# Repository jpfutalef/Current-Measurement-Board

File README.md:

# Power-Monitoring-Board
This repo contains scripts, details and specifications for a board designed to measure very low power consumption in MCU's with high accuracy.

## Goals

The goal here is to develop a simple current measuring board that can measure from 1uA - 50mA at high frequencies (>10kHz).

This board has to be easy to connect to a computer or a raspberry, minimizing cable connections. The idea is to have a single board with two usb ports, one to connect to the PC and the other to an IoT node with any usb connection (micro, mini, etc.).

## Organization

The repo is organized as follows,

* **ltspice**: in this folder can be found the different spice schematics to simulate the different current measurement boards.
* **scripts**: in this folder can be found different c, python, etc. scripts used to read data from the current measurement circuit or calibrate the respective board.
* **boards**: the actual eagle schematics can be found in this folder, either for the circuits or breakout's for small smd-components.

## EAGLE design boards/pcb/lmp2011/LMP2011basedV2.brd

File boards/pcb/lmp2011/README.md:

# PCB eagle schematics and boards for LMP2011

LMP2011 is a precision OPAMP. This device uses auto-zero techniques to continually correct the input offset error voltage. The input offset is 60uV in the worst case scenario,  0.8uV typically. Furthermore has a typical CMRR of 130dB, its minimum is 95dB.

## Notations
* Current Measuring Board (CMB): PCB with the designed circuit that can measure shunt voltage, and supply voltage.
* mcu: microcontroller connected to the CMB, its performs calibrations and translate the supply voltage and current measurements.
* Node: target mcu which power consumption the CMB is measuring.

## How to use

* Connect switch controllers (SWITCH_CTRL_1 to SWITCH_CTRL_5) to 5 different GPIO on any mcu.
* Connect low current, high current and supply voltage to 3 different ADC input in the mcu
* Power the CMB, either from the micro usb port or with 5V from an external power supply
* Bypass the targeted node power supply by either connecting it's power source to VBAT or the USB port on CMB.
* If the targeted node supply source is connected to VBAT then the node can be powered by connecting it's power input to VMCU, if it's USB powered a jumper must be connected between 5V and VBAT on CMB.

## Specifications:
- Power supply: 5V from USB port
- Current range: ~10uA - 50mA
- First stage gain: x100
- Second stage gain: x197 for low current, x1.51 for high current

## How version 2 works(detailed)

This board has a similar operation as the design using MAX4239, except that in this case the CMB does not include a DC booster (TODO: check if it is neccesary).

### Fist stage

The first stage amplifies the voltage difference in the shunt resistance through an OPAMP. R1, R2, R4 and R5 form a x100 gain between VBAT y VS-. R27 and C2 are added for stability purposes. 

### Second stage

The second stage has a LTC6241 high precision dual opamp. There are two current ranges with different gains:

- Low current range: 0uA-600uA, x197 gain
- High current tange: 600uA-50mA, x1.51 gain

These gains values adjust to the ADC input ranges. The 49.9 resistor are put in place to isolate the amplifier output and ADC input, thus preventing oscillation.

4 usually open analog switches are used for calibration in low current, this is done by measuring current flow threw resistors R9, R10, R13 and R14. TS5A23166DCUR switches where chosen for their high voltage input range, high max current and low Ron (0.8 ohms).

A normally closed switch is connected between the target node and it's supply source. The TS5A23167DCUR was chosen with similar characteristics as the TS5A23167DCUR.

C1 capacitor is connected between the supply source and ground to stabilize supply voltage from power source.

The buffer stage to measure the supply source uses a LTC6240 high precision amplifier with a x0.5 gain stage to allow supply voltage higher than the mcu supply (3.3V) to be converted with the ADC. This buffer stages also isolated the two.

As a supply source a microUSB type B female connector is used. This gives a 5V power supply. To reduce high frequency noise a high impedance, low frequency ferrite is used (1K@1Mhz).

A female type A USB connector can be used to power the targeted node. Analog and digital ground are separated by using two schottky diodes, CUS08F30 because of their high response and low activation voltage.

### Available connections

Multiple input/output pins are exposed to users: 

- SWITCH_CTRL_1: switch's on power supply for targeted node.
- SWITCH_CTRL_2 a 5: switches on or off calibration resistors.
- VMCU: output voltage that powers the targeted node it's short-circuited to the female type A USB.
- GND: ground
- OUT_STAGE1: first amplifying stage gain output, for debugging purposes.
- VS-: shunt resistor low voltage pin.
- VBAT: pin where targeted node supply voltage is connected to bypass it.
- +5V: 5V output, its separated from the USB by the ferrite. de 5V, separada de USB por la ferrita.

# Board versions

## LMP2011 V1 - Fabricated
This version of the board was manufactured with [OSHPARK](https://oshpark.com/). Soldering and testing was done at Inria Chile office.

### Overview

This board needs a 5V supply for most of the IC, LMP2011 get supply from a DC booster in the CMB.

The first stage is a differential amplifier with x10 gain, the second stage has a low current stage with x197 gain and a high current range with x1.51 gain.

To read supply voltage a x0.5 buffer stage is used.

Analog and digital ground are separate with schottky diodes.

5V supply source is filtered with a 1k@1MHz ferrite.

USB enclosure is connected to the digital ground.

### Testing conclusions

#### Remarks
- Manufactured board
- Soldered components
- All IC had correct supply and GND connections
- There is an error in power supply for the LMP2011 design: it can't be supply from 8v68. MIC2250 is not connected and bypass 5V to the supply pin of the IC.
- There aren't conclusive results from the circuit. The CMB with this IC does not work as it should, neither in a breadboard.

#### TODO
- Check connections in LMP2011
- Check real measurement range
- Make reading with a mcu. Calibrate and control of the switches

#### Issues
- LMP2011 not working correctly
- The gain in low current stage should be x197, not x19.7 10K resistance should be a 1K
- Control switch for node supply are not connected well. This was fixed soldering directly from the inputs of the switch
- Ad
- VBAT and VADC silkscreen names are misplaced, they are switched.
- There are no pull-down resistors in the control switch

#### To improve
- CMRR by using higher tolerance resistor values, at least 0.1%. This can also be done by incrementing the stages gain, but this affects the current ranges
- Change USB port from SMD to thru-hole to improve robustness in the pcb
- Different configurations for the first stage should be considered

## LMP2011 V2 - not manufactured

This version of the board should solve the issues from the last version manufactured.

* Remove DC booster (Check supply needed from the IC)
* Low current gain is addressed by changing 10K resistors to 1K
* Switch connection is fixed
* Pull down resistors are included for the switches

There is only the schematic for this board, not the board design yet

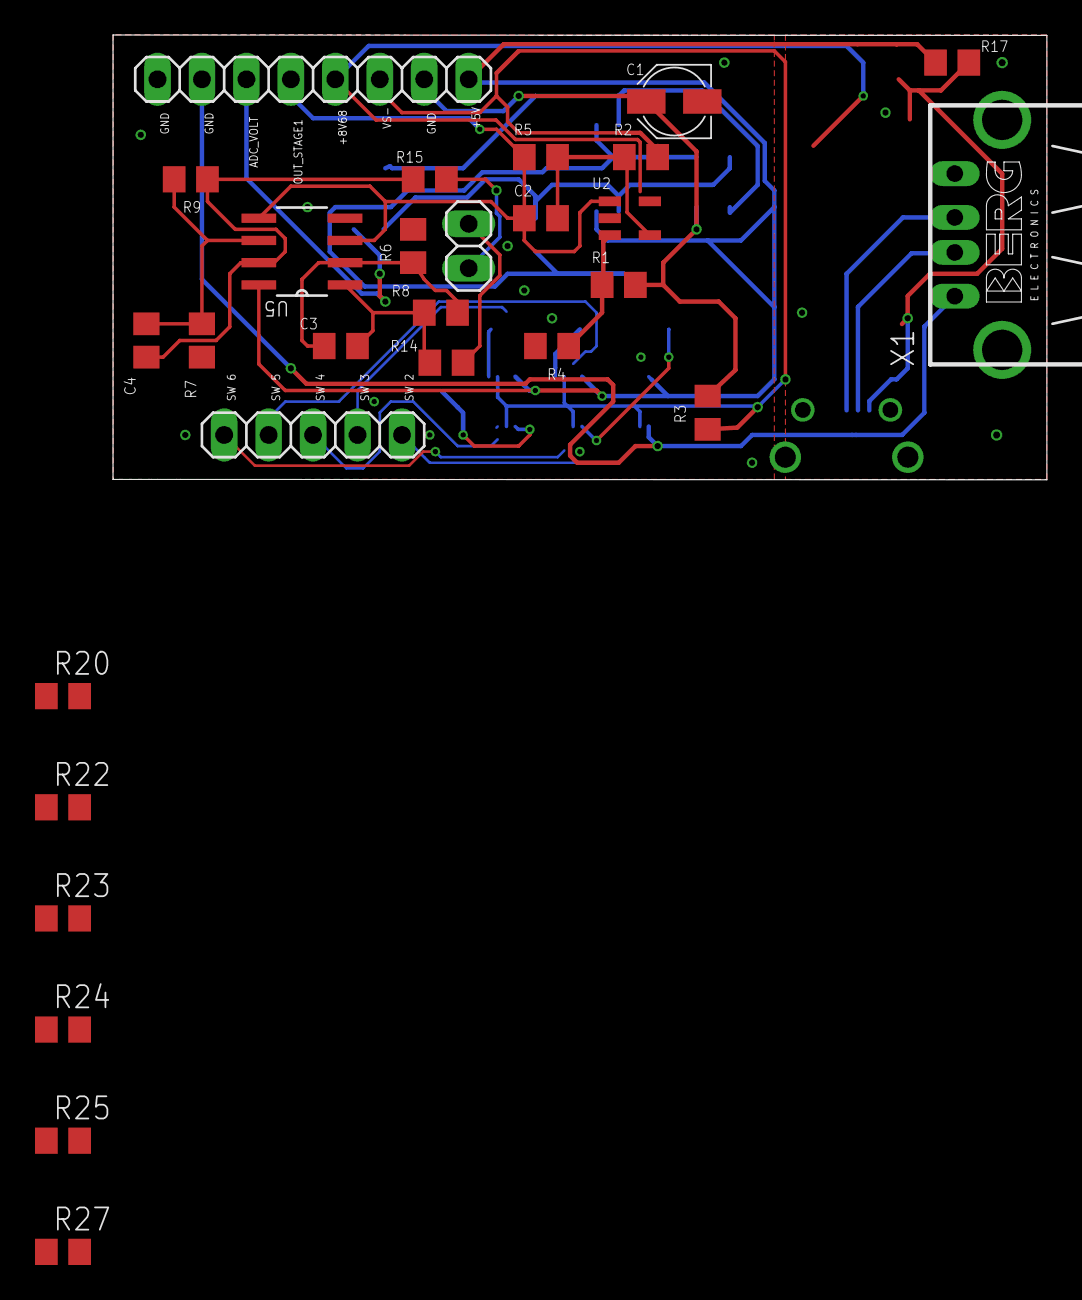
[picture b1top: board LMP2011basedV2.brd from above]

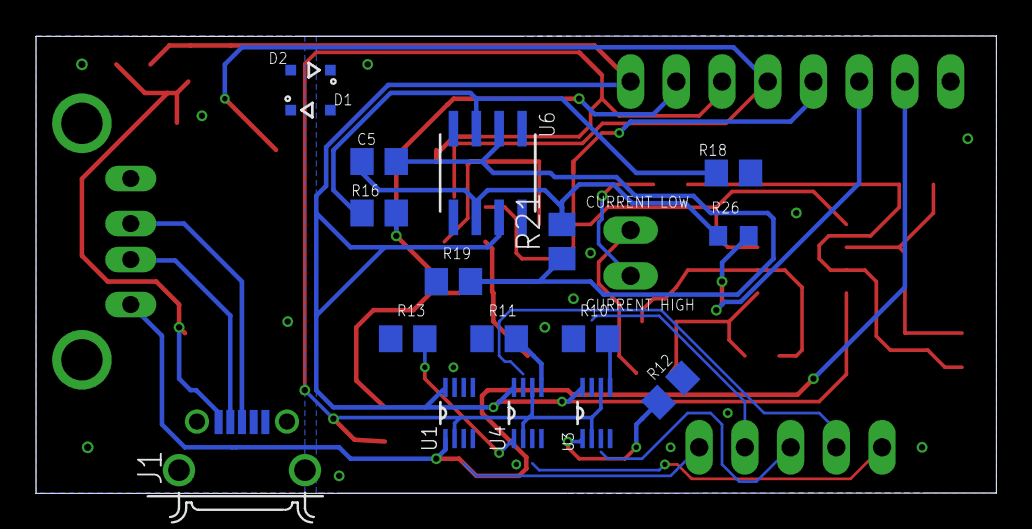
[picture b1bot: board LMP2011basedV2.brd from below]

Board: 2 copper layers, 53.4 x 25.4 mm, 45 parts (17 on the bottom side), 31 nets.

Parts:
C1: 1u; PANASONIC_B
C2, C3, C4, C5: 10p; C0805
D1, D2: CUS08F30; SOD323
J1: 10118194-0001LF; FRAMATOME_10118194-0001LF
JP1: ADC_CURR; 1X02
JP2: SWITCH_PINS; 1X05
JP3: UTILITY1; 1X08
R1, R6, R11, R27: 1k; R0805
R2, R13, R18, R21: 10k; R0805
R3: 4R7; R0805
R4, R5, R7, R10, R20, R22, R23, R24, R25: 100k; R0805
R8: 187k; R0805
R9: 51k; R0805
R12: 1M; R0805
R14, R15: 49.9; R0805
R16, R19: 20k; R0805
R17: 1K@1MHz; R0805
R26: 49.9; R0603
U1: TS5A23167DCUR; SOP50P310X90-8N
U2: LMP2011MF; SOT95P285X120-5N
U3, U4: TS5A23166DCUR; SOP50P310X90-8N
U5: LTC6241CS8PBF; SOIC127P600X175-8N
U6: LTC6240CS8PBF; SO-8_S
X1: PN87520-S

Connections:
+5V: JP3.8, R17.1, U1.8, U2.5, U3.8, U4.8, U5.8, U6.7
+5V_USB: J1.1, R17.2
ADC_CURRENTHIGH: JP1.2, R15.1
ADC_CURRENTLOW: JP1.1, R14.1
ADC__VOLT: JP3.3, R26.2
D+: J1.3, X1.3
D-: J1.2, X1.2
DGND: D1.A, D2.C, J1.5, X1.4, X1.S1, X1.S2
GND: C1.-, D1.C, D2.A, JP3.1, JP3.5, R4.1, R6.2, R7.2, R10.1, R11.1, R12.1, R13.1, R18.1, R19.1, R20.1, R22.1, R23.1, R24.1, R25.1, R27.2, U1.4, U2.2, U3.4, U4.4, U5.4, U6.4
unnamed: R16.1, R18.2, U6.3
unnamed: C5.1, R21.2, R26.1, U6.6
unnamed: C5.2, R19.2, R21.1, U6.2
unnamed: C3.1, R8.1, R14.2, U5.1
unnamed: C2.2, R2.1, R5.2, U2.4
unnamed: C4.1, R9.1, R15.2, U5.7
unnamed: R1.1, R4.2, U2.3
unnamed: C3.2, R6.1, R8.2, U5.2
unnamed: C4.2, R7.1, R9.2, U5.6
OUT_STAGE1: C2.1, JP3.4, R5.1, R27.1, U2.1, U5.3, U5.5
SW3_CON: R12.2, U3.1
SW4_CON: R10.2, U3.5
SW5_CON: R13.2, U4.1
SW6_CON: R11.2, U4.5
SWITCH_CTRL_1: JP2.1, R20.2, U1.3, U1.7
SWITCH_CTRL_2: JP2.2, R22.2, U3.7
SWITCH_CTRL_3: JP2.3, R23.2, U3.3
SWITCH_CTRL_4: JP2.4, R24.2, U4.7
SWITCH_CTRL_5: JP2.5, R25.2, U4.3
VBAT: C1.+, JP3.7, R1.2, R3.2, R16.2
VMCU: JP3.2, U1.1, U1.5, X1.1
VS-: JP3.6, R2.2, R3.1, U1.2, U1.6, U3.2, U3.6, U4.2, U4.6

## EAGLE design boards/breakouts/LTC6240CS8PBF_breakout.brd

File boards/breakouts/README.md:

## SMD breakout's

This folder contains SMD breakouts for the smallest SMD IC used for this project.

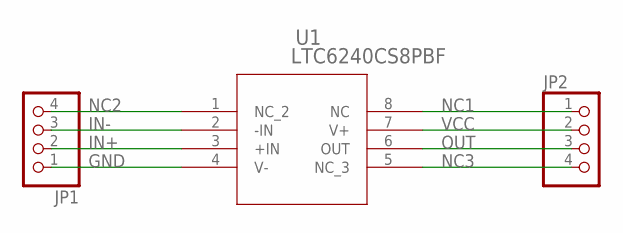
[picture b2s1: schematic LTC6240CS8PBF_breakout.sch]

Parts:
JP1, JP2: PINHD-1X4; 1X04
U1: LTC6240CS8PBF; SO-8_S

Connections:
GND: JP1.1, U1.4 (V-)
IN+: JP1.2, U1.3 (+IN)
IN-: JP1.3, U1.2 (-IN)
NC1: JP2.1, U1.8 (NC)
NC2: JP1.4, U1.1 (NC_2)
NC3: JP2.4, U1.5 (NC_3)
OUT: JP2.3, U1.6 (OUT)
VCC: JP2.2, U1.7 (V+)

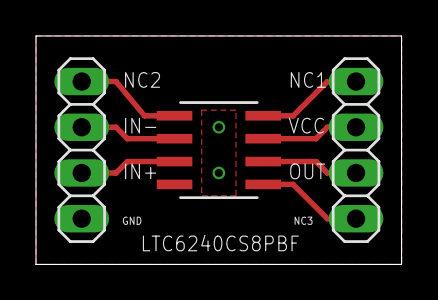
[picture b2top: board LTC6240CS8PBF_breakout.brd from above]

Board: 2 copper layers, 20.3 x 12.7 mm, 3 parts (0 on the bottom side), 8 nets.

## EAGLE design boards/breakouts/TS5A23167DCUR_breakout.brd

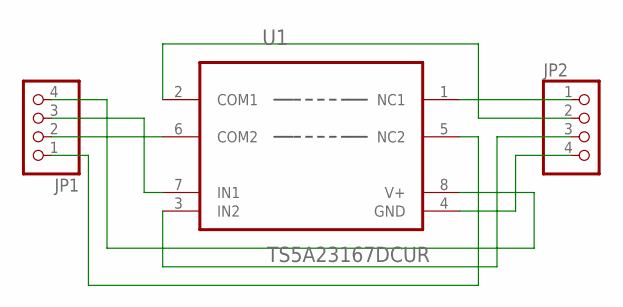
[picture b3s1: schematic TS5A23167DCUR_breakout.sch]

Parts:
JP1, JP2: PINHD-1X4; 1X04
U1: TS5A23167DCUR; SOP50P310X90-8N

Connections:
COM1: JP2.2, U1.2 (COM1)
COM2: JP1.2, U1.6 (COM2)
GND: JP2.4, U1.4 (GND)
IN1: JP1.3, U1.7 (IN1)
IN2: JP2.3, U1.3 (IN2)
NO1: JP2.1, U1.1 (NC1)
NO2: JP1.1, U1.5 (NC2)
VCC: JP1.4, U1.8 (V+)

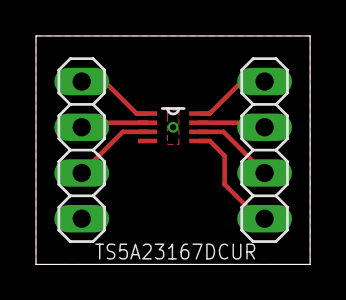
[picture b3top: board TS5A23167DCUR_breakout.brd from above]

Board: 2 copper layers, 15.2 x 12.7 mm, 3 parts (0 on the bottom side), 8 nets.

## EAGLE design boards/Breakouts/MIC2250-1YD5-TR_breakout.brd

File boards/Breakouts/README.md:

Breakout para los componentes usados en la placa para medición.

Útiles para componentes de tamaño reducido.

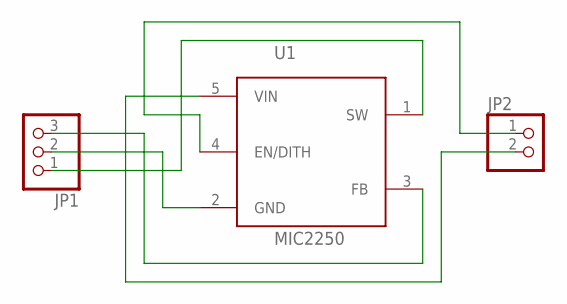
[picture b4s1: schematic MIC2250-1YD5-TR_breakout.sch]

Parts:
JP1: PINHD-1X3; 1X03
JP2: PINHD-1X2; 1X02
U1: MIC2250; SOT95P270X145-5N

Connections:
EN/DITH: JP2.1, U1.4 (EN/DITH)
FB: JP1.3, U1.3 (FB)
GND: JP1.2, U1.2 (GND)
SW: JP1.1, U1.1 (SW)
VIN: JP2.2, U1.5 (VIN)

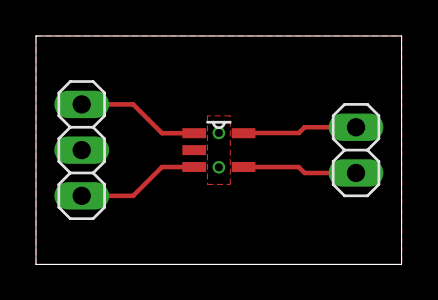
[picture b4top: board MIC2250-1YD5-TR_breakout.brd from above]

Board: 2 copper layers, 20.3 x 12.7 mm, 3 parts (0 on the bottom side), 5 nets.

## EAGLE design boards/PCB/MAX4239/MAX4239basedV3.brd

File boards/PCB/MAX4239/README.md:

# PCB eagle schematics and boards for MAX 4239

El MAX4239 es un OP AMP auto-zero, con un voltaje offset de entrada de 0.1uV tipico y 2uV en todo el rango de temperatura, además de un CMRR de  120dB minimos y 140dB típico.

### Cómo usar

Considerando que se tiene una placa compatible con RIOT:

- Conectar los controles de switch (SWITCH_CTRL_1 a SWITCH_CTRL_5) a GPIO.
- Conectar las salidas de low current, high current y adc volt (medición de supply) a las entradas analógicas.
- Conectar alimentación a entrada micro USB desde computadora o 5V.
- Conectar alimentación del MCU objetivo a VBAT. En caso de querer alimentar todo desde la alimentación USB, conectar un jumper entre 5V y VBAT.
- Si el MCU objetivo puede ser conectado por USB, utilizar el puerto USB tipo A. Este puerto mantiene la comunicación serial.
- En caso de no poder utilizar un USB, la alimentación del MCU objetivo puede obtenerse desde VMCU.

### Especificaciones:
- Alimentación de 5V desde USB
- Rango(ideal): ~1uA - 50mA
- Primera etapa ganancia de 100
- Segunda etapa amplifica 197 para bajas corrientes y 1.51 para altas corrientes.

### Working of current version (3) (detailed)

La primera etapa se encarga de amplificar el voltage en la resistencia de Shunt mediante configuracion de amplificador diferencial. Las resistencias R1,R2,R4 y R5 conforman una ganancia diferencial de 100 (100k/1k) entre VBAT y VS- (terminales de la resistencia de shunt). R6 y C3 son añadidos para estabilidad, C3 además ayuda a disminuir los peaks de carga del auto-zero. C2 ayuda a mantener la fuente estable.

La segunda etapa es conformada por un DUAL OP AMP LTC6241 de alta precision. Hay dos rangos de medicion que tienen distintas ganancias cada uno:
- Low current range: 0uA-600uA
- High current tange: 600uA-50mA

Para corrientes bajas, la segunda etapa amplifica x197. Para corrientes altas solo se amplifica x1.51. Estas ganancias acomodan el voltaje a los rangos del ADC. Las resistencias de 49.9R son utiles para aislar la salida del amplificador y evitar oscilaciones.

Se utilizan 4 switch analogos normalmente abiertos para calibrar la medición en corrientes pequeñas utilizando las resistencias R9, R10, R13 y R14. Los TS5A23166DCUR son elegidos debido al alto voltaje soportado en sus entradas, alta corriente máxima y baja resistencia (0.7 omhs aprox.). En cambio, se elige un switch normalmente cerrado para la alimentación del MCU objetivo, un TS5A23167DCUR, de características equivalentes al TS5A23166DCUR. El capacitor C1 es puesto entre la alimentación del MCU objetivo para asegurar estabilidad.

La etapa de buffer para la fuente de poder utiliza un LTC6240 de alta precision, configurado a ganancia x0.5 con tal de evitar que valores altos de voltajes no puedan ser leidos por ADC de referencias de voltaje bajo (5V fuente -> 2.5V ADC puede ser leido con referencia de 3.3V). Además permite aislar el nodo del ADC.

Para la alimentación, se utiliza una entrada micro USB tipo B hembra, que proporciona 5V desde una computadora o cargador. En caso de uso con la computadora, se han cortocircuitados las líneas de datos D+ y D-. Para evitar el ruido de alta frecuencia del computador, se utiliza una ferrita de alta impedancia a baja frecuencia (1K@1Mhz). Un conector hembra USB tipo A proporciona la salida del circuito para alimentar al MCU objetivo. Finalmente, se separa la tierra virtual de la digital mediante diodos schottky CUS08F30 debido a su rápida respuesta y bajo voltaje de activación.

Diversos pines de utilidad son puestos a disposición del usuario. Estos permiten alimentar con fuente externa, observar las salidas de las distintas etapas, controlar switchs, etc. Las resistencias 21 a 25 son de pull down.

- SWITCH_CTRL_1: controla apertura del switch que proporciona energia al MCU.
- SWITCH_CTRL_2 a 5: controla cierre de switch a resistencias de calibracion.
- ADC_VOLT: salida buffer supply.
- VMCU: voltaje que se entrega al MCU objetivo. En corto circuito con el usb.
- GND: tierra
- OUT_STAGE1: salida primera etapa correinte.
- VS-: pata negativa resistencia de shunt.
- VBAT: voltaje con el que se supone se alimenta el MCU.
- +5V: salida de 5V, separada de USB por la ferrita.

El MAX4239 puede ser alimentado hasta 6V. Sin embargo en sus entradas diferenciales sólo pueden ingresar hasta aproximadamente 0.3V más que la fuente de voltaje del MAx4239. De todas formas, se ha observado que para entradas de 5V (que pueden provenir de un USB) correspondientes a una de las patas de la resistencia de shunt provoca oscilaciones. Esto debiese solucionarse alimentando al MAX4239 con 5.5V utilizando un DC booster MIC2250 fijado a 5.5V. La configuracion usada es la recomendada por el fabricante.

# Versiones placas

## MAX4239 V1 (no prototipada)
Esquemático es equivalente al de la versión 2. El único cambio es de la pcb board que se descarta por ser de gran tamaño y no tener bien las reglas de diseño.

## MAX4239 V2 (prototipada)
Esta versión de la placa fue prototipada. La PCB fue manufacturada por OSHPARK y los componentes fueron comprados en DigiKey. El soldado de componentes y pruebas de laboratorio fueron realizados en el IOT LAB de Inria Chile.

### Acerca de

Esta versión de la placa considera una alimentación de 5V para todos los IC, proveniente de la entrada micro USB.

La primera etapa es un amplificador diferencial de ganancia 10. La segunda etapa consta de los rango Low Current (ganancia de 19,7) y high current (ganancia de 1,51).

Para lecturas de la alimentacion del MCU objetivo, se utiliza una etapa que reduce el voltage a la mitad.

Tierras digital y analoga son separadas con diodos schottky.

Fuente de 5v de USB es filtrada con ferrita 1k@1MHz.

La carcasa del USB tipo A es conectado a tierra digital.

### Conclusiones a partir del prototipado de la placa

#### Observaciones
- Placa manufacturada
- Soldado de componentes OK
- Todos los IC reciben alimentación debida.
- Todos los IC reciben tierra debida.
- Conectando multiples resistencias para emular consumo se han logrado medir en el alto rango corrientes de 600uA.
- Utilizando los switch para calibrar con las resistencias, se han observado valores que debiesen permitir calibrar.

#### Qué falta hacer
- Checkear el rango efectivo de medición.
- Realizar medición con microcontrolador. Que este haga la calibración y controle los switches.

#### Issues
- Para alimentación de 5V se observan oscilaciones en la primera etapa. Se han agragado resistencias de 1KHz a tierra a la salida, observándose disminución aún continúa. El problema es solucionado alimentando externamente el circuito con 5.5V o más. Se concluye que el problema es debido a que en las entradas del MAX4239 hay un máximo de voltaje limitado por la alimentación.
- Condensador C2 está mla puesto, debe conectarse a tierra. De todas formas puede quitarse y hacer un puente sin problemas.
- La ganancia de la etapa de low current debiese ser 187, no 19,7. Esto fue debido a que la resistencia de 10K es incorrecta, debiese ser de 1K.
- Los switch de control de alimentación al MCU están mal conectados. Esto fue solucionado soldando un cable a las patas que lo controlan.
- Agregar resistencias de pulldown a los controles de los switch como precaución en caso de no existir.
- En la placa, hay nombres en la silkscreen cambiados.
- Con respecto al laboratorio: muchos problemas de estática, ocurrieron muchos casos de descarga electroestática que producían oscilaciones en el circuito y que podrían dañar a IC. El osciloscopio tiene un problema, en cierto momento se detiene y debe ser reiniciado, al momento de reiniciarse el canal 1 siempre ponía impedancia de 50ohm e invertido, afectando la observación.

#### Qué se podría mejorar
- Mejorar CMRR incrementando tolerancia de TODAS las resistencias, que sean de 0,1% o menos. También puede incrementarse aumentando la ganancia diferencial, pero esto afecta los rangos de medición.
- Los micro USB ojalá que sean Thru-hole para evitar que se salgan.
- Para el switch que entrega alimentación al MCU objetivo, unir los dos switch y así permitir más paso de corriente.

#### Tips
- Uso de pasta de soldar y pistola de calor es recomendable para componentes de tamaño muy reducido
- Cautín de punta plana y malla de cobre con flux ayuda a remover exceso de estaño
- USB thru-hole ojalá soldar con estaño de alto punto de fusión pues es más duro
- Descarga a tierra puede hacerse con salida a tierra de los equipos

## MAX4239 V3 (no prototipada)

Esta versión debiese solucionar todos los issues presentados en la versión anterior.
- El problema de la alimentación es solucionado utilizando un DC booster que entregue 5V5 de alimentación (MIC2250).
- C2 está bien puesto.
- La ganancia de low current es solucionada cambiando la resistencia de 10K por 1K.
- Los switch están bien conectados y reorganizados.
- Se incluyen resistencias de pull-down en las lineas de control de los switch.

La placa aún no se ha diseñado, sólo está el esquemático.

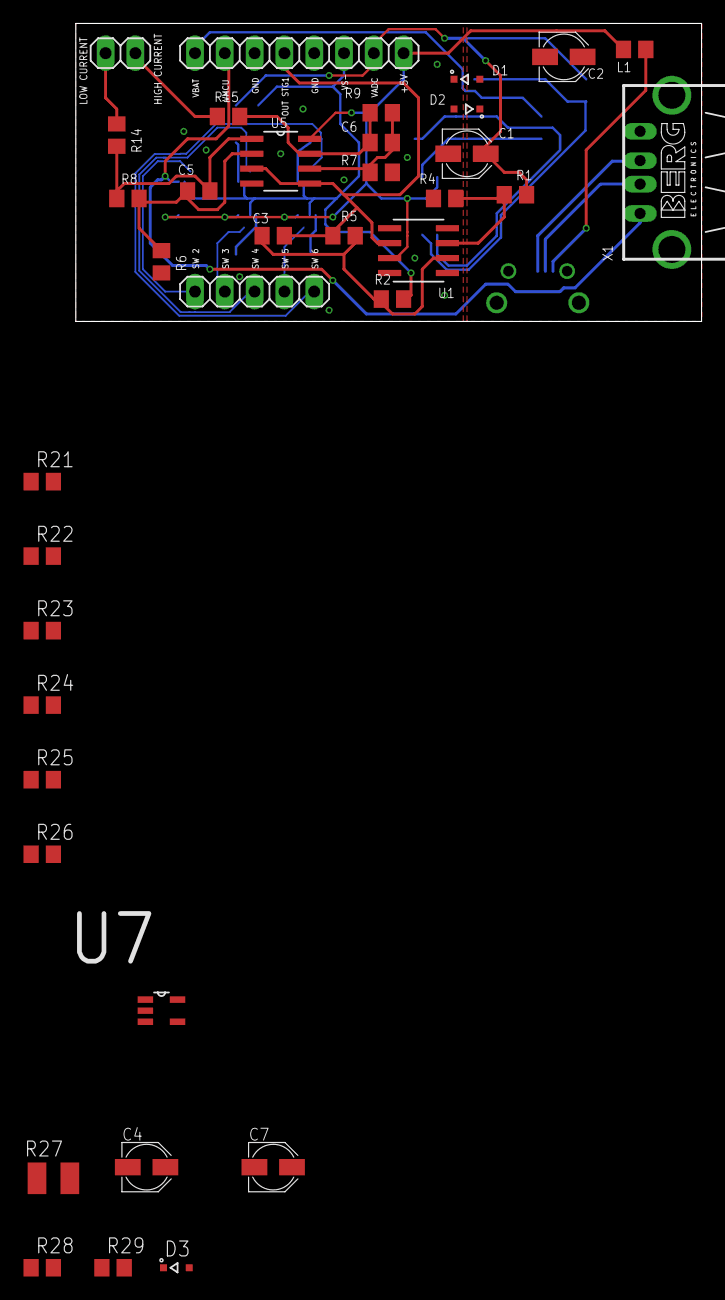
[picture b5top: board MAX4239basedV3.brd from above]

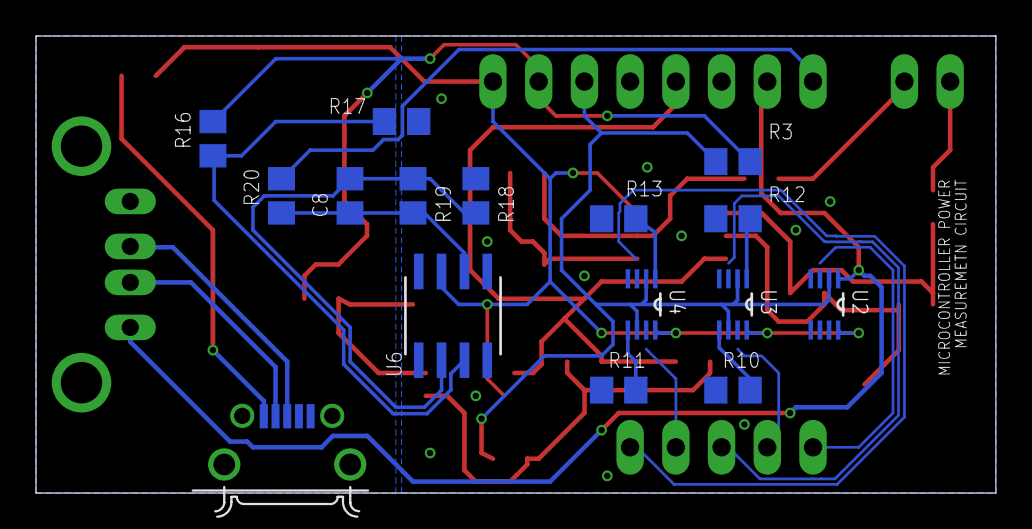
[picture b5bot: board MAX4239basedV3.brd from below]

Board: 2 copper layers, 53.3 x 25.4 mm, 53 parts (16 on the bottom side), 34 nets.

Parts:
C1: 0.1u; PANASONIC_B
C2: 1m; PANASONIC_B
C3, C5, C6, C8: 10p; C0805
C4: 2u; PANASONIC_B
C7: 10u; PANASONIC_B
D1, D2, D3: CUS08F30; SOD323
J1: 10118194-0001LF; FRAMATOME_10118194-0001LF
JP1: ADC_CURR; 1X02
JP2: SWITCH_PINS; 1X05
JP4: UTILITY2; 1X08
L1: 1K@1MHz; R0805
R1, R2, R26: 1k; R0805
R3: 4R7; R0805
R4, R5, R7, R21, R22, R23, R24, R25: 100k; R0805
R6, R17, R19, R29: 10k; R0805
R8: 187k; R0805
R9: 51k; R0805
R10: 100K; R0805
R11: 1K; R0805
R12: 1M; R0805
R13: 10K; R0805
R14, R15, R20: 49.9; R0805
R16, R18: 20k; R0805
R27: 10uH; R1210
R28: 35k; R0805
U1: MAX4239ASA; 21-0041B_8
U2: TS5A23167DCUR; SOP50P310X90-8N
U3, U4: TS5A23166DCUR; SOP50P310X90-8N
U5: LTC6241CS8PBF; SOIC127P600X175-8N
U6: LTC6240CS8PBF; SO-8_S
U7: MIC2250; SOT95P270X145-5N
X1: PN87520-S

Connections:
+5V: C7.+, JP4.8, L1.1, R27.1, U2.8, U3.8, U4.8, U5.8, U6.7, U7.4, U7.5
+5V5: C2.+, C4.+, D3.C, R28.2, U1.1, U1.7
+5V_USB: J1.1, L1.2
ADC_CURRENTHIGH: JP1.2, R15.1
ADC_CURRENTLOW: JP1.1, R14.1
ADC__VOLT: JP4.1, R20.2
D+: J1.3, X1.3
D-: J1.2, X1.2
DGND: D1.A, D2.C, J1.5, U7.2, X1.4, X1.S1, X1.S2
FB: R28.1, R29.2, U7.3
GND: C1.-, C2.-, C4.-, C7.-, D1.C, D2.A, JP4.3, JP4.5, R4.1, R6.2, R7.2, R10.1, R11.1, R12.1, R13.1, R17.1, R18.1, R21.1, R22.1, R23.1, R24.1, R25.1, R26.1, R29.1, U1.4, U2.4, U3.4, U4.4, U5.4, U6.4
unnamed: R16.1, R17.2, U6.3
unnamed: C8.1, R19.2, R20.1, U6.6
unnamed: C8.2, R18.2, R19.1, U6.2
unnamed: C5.1, R8.1, R14.2, U5.1
unnamed: C3.2, R2.1, R5.2, U1.2
unnamed: C6.1, R9.1, R15.2, U5.7
unnamed: R1.1, R4.2, U1.3
unnamed: C5.2, R6.1, R8.2, U5.2
unnamed: C6.2, R7.1, R9.2, U5.6
OUT_STAGE1: C3.1, JP4.4, R5.1, R26.2, U1.6, U5.3, U5.5
SW: D3.A, R27.2, U7.1
SW3_CON: R12.2, U3.1
SW4_CON: R10.2, U3.5
SW5_CON: R13.2, U4.1
SW6_CON: R11.2, U4.5
SWITCH_CTRL_1: JP2.1, R21.2, U2.3, U2.7
SWITCH_CTRL_2: JP2.2, R22.2, U3.7
SWITCH_CTRL_3: JP2.3, R23.2, U3.3
SWITCH_CTRL_4: JP2.4, R24.2, R25.2, U4.7
SWITCH_CTRL_5: JP2.5, U4.3
VBAT: C1.+, JP4.7, R1.2, R3.2, R16.2
VMCU: JP4.2, U2.1, U2.5, X1.1
VS-: JP4.6, R2.2, R3.1, U2.2, U2.6, U3.2, U3.6, U4.2, U4.6

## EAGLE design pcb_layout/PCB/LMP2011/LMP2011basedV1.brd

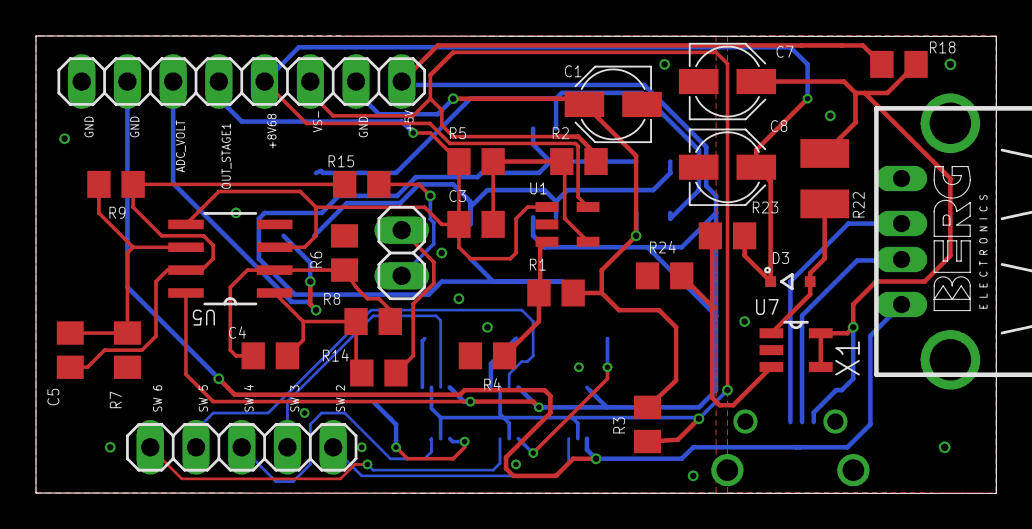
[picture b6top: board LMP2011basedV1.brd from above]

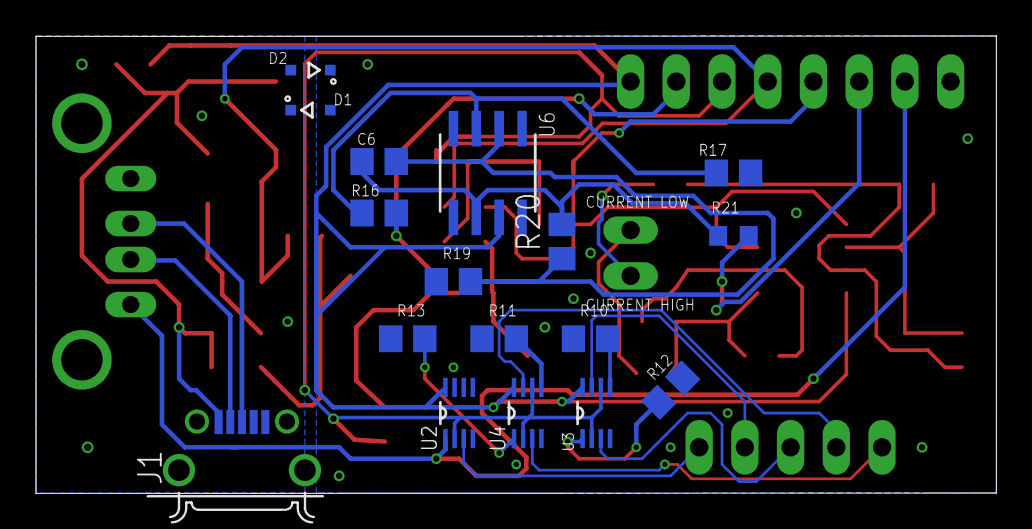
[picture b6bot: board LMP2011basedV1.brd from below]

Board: 2 copper layers, 53.4 x 25.4 mm, 46 parts (17 on the bottom side), 34 nets.

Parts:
C1: 1u; PANASONIC_B
C3, C4, C5, C6: 10p; C0805
C7: 10u; PANASONIC_B
C8: 2u; PANASONIC_B
D1, D2, D3: CUS08F30; SOD323
J1: 10118194-0001LF; FRAMATOME_10118194-0001LF
JP1: ADC_CURR; 1X02
JP2: SWITCH_PINS; 1X05
JP3: UTILITY1; 1X08
R1, R2, R6, R12, R17, R20, R24: 10k; R0805
R3: 4R7; R0805
R4, R5, R7, R11: 100k; R0805
R8: 187k; R0805
R9: 51k; R0805
R10: 1k; R0805
R13: 1M; R0805
R14, R15: 49.9; R0805
R16, R19: 20k; R0805
R18: 1K@1MHz; R0805
R21: 49.9; R0603
R22: 10uH; R1210
R23: 60k4; R0805
U1: LMP2011MF; SOT95P285X120-5N
U2: TS5A23167DCUR; SOP50P310X90-8N
U3, U4: TS5A23166DCUR; SOP50P310X90-8N
U5: LTC6241CS8PBF; SOIC127P600X175-8N
U6: LTC6240CS8PBF; SO-8_S
U7: MIC2250; SOT95P270X145-5N
X1: PN87520-S

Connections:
+5V: JP3.8, R18.1, U2.8, U3.8, U4.8, U5.8, U6.7
+5V_USB: C7.+, J1.1, R18.2, R22.1, U7.4, U7.5
+8V68: C8.+, D3.C, JP3.5, R23.2, U1.5
ADC_CURRENTHIGH: JP1.2, R15.1
ADC_CURRENTLOW: JP1.1, R14.1
ADC__VOLT: JP3.3, R21.2
D+: J1.3, X1.3
D-: J1.2, X1.2
DGND: D1.A, D2.C, J1.5, U7.2, X1.4, X1.S1, X1.S2
FB: R23.1, R24.2, U7.3
GND: C1.-, C7.-, C8.-, D1.C, D2.A, JP3.1, R4.1, R6.2, R7.2, R10.1, R11.1, R12.1, R13.1, R17.1, R19.1, R24.1, U1.2, U2.4, U3.4, U4.4, U5.4, U6.4
unnamed: R16.1, R17.2, U6.3
unnamed: C6.1, R20.2, R21.1, U6.6
unnamed: C6.2, R19.2, R20.1, U6.2
unnamed: C4.1, R8.1, R14.2, U5.1
unnamed: C3.2, R2.1, R5.2, U1.4
unnamed: C5.1, R9.1, R15.2, U5.7
unnamed: R1.1, R4.2, U1.3
unnamed: C4.2, R6.1, R8.2, U5.2
unnamed: C5.2, R7.1, R9.2, U5.6
OUT_STAGE1: C3.1, JP3.4, R5.1, U1.1, U5.3, U5.5
SW: D3.A, R22.2, U7.1
SW3_CON: R12.2, U3.1
SW4_CON: R10.2, U3.5
SW5_CON: R13.2, U4.1
SW6_CON: R11.2, U4.5
SWITCH_CTRL_2: JP2.1, U2.3
SWITCH_CTRL_3: JP2.2, U3.7
SWITCH_CTRL_4: JP2.3, U3.3
SWITCH_CTRL_5: JP2.4, U4.7
SWITCH_CTRL_6: JP2.5, U4.3
VBAT: C1.+, JP3.7, R1.2, R3.2, R16.2
VMCU: JP3.2, U2.1, X1.1
VS-: JP3.6, R2.2, R3.1, U2.2, U3.2, U3.6, U4.2, U4.6

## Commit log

2018-01-10 Add existing file
2018-01-10 Readme update
2018-01-11 INA226 script
2018-01-11 INA226 commit
2018-01-11 INA script
2018-01-15 PCB layouts
2018-01-23 RIOT, new PCB layouts and scripts
2018-01-31 spice models, scripts and pcb layouts update
2018-01-31 python script
2018-01-31 readme for script in power_measure
2018-01-31 update folder
2018-01-31 renombrado: README -> README.md
2018-01-31 modificado: README.md
2018-01-31 gitignore
2018-01-31 Added stage images for MAX4239 circuit and README
    nuevo archivo: pcb_layout/PCB/LMP2011/README.md
    nuevo archivo: pcb_layout/PCB/MAX4239/Images/IM1.png
    nuevo archivo: pcb_layout/PCB/MAX4239/Images/IM2.png
    nuevo archivo: pcb_layout/PCB/MAX4239/Images/IM3.png
    nuevo archivo: pcb_layout/PCB/MAX4239/Images/IM4.png
    nuevo archivo: pcb_layout/PCB/MAX4239/Images/IM5.png
2018-01-31 Modified README for MAX4239
2018-01-31 update pictures and README for MAX4239
2018-01-31 Added figures for LMP2011
2018-02-05 reorder directories
2018-02-05 remove RIOT for folder directory
2018-02-05 apply styling, modify readmes
2018-02-07 Readme updato for PCB folder, MAX4239, scripts folder and added ltspice README.
2018-02-07 Readme update for PCB folder, MAX4239, scripts folder and added ltspice README.
2018-02-07 Fixed issue with figures in max4239 readme
2018-02-07 Update in MAX4239 readme
2018-02-07 add binary and object files, among others to gitignore
2018-02-07 refactor node_measurement code
2018-02-07 Added spice models for MAX4239 & LMP2011 in ltspice/Spice Models. In the same directory, created a readme file about them. Update PCB readme file, MAX4239 figures directory, MAX4239 readme file, scri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
2018-02-07 Updated MAX4239 readme
2018-02-07 Added figures for LMP2011, update MAX4239 readme and LMP2011 readme
2018-02-08 --fixup: name styles
2018-02-08 name styling, wip on translating some doc
2018-02-08 --fixup: fix images relative paths
2018-02-08 --fixup: fix lmp2011 readme image linking
2018-02-08 translate max4239 doc
2018-02-09 translate lmp readme doc
2018-02-09 change mayus in readme
2018-02-09 fix oshpark link
2018-02-14 Add author to scripts in adc_riot_test, arduino_ina226 and master.py in power_measure. Add photos of prototiped board
